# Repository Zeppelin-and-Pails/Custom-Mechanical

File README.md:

# Custom-Mechanical
Resources and tutorials for creating a custom mechanical keyboard

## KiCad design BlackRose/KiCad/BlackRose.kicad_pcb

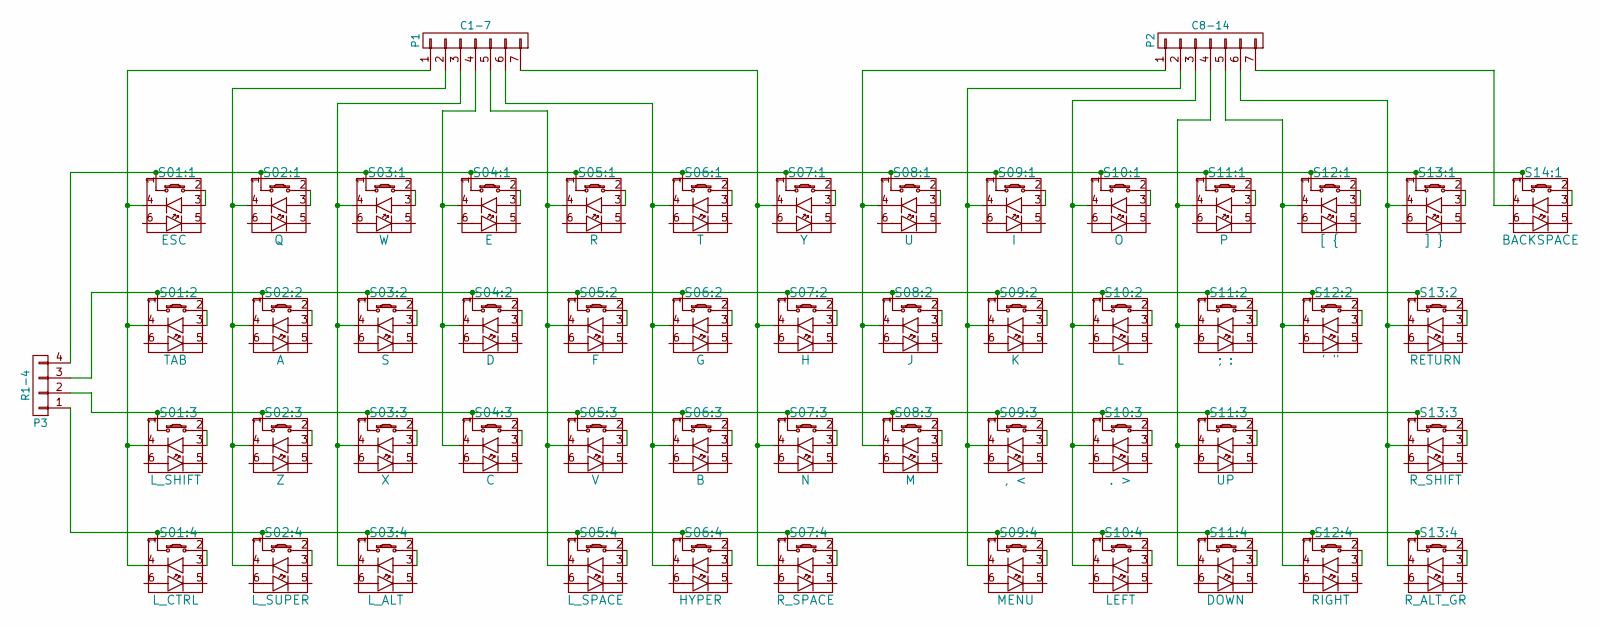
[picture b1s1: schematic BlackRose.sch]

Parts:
P1: C1-7; Pin_Header_Straight_1x07
P2: C8-14; Pin_Header_Straight_1x07
P3: R1-4; Pin_Header_Straight_1x04
S01:1: ESC; CHERRY_PCB_100H
S01:2: TAB; CHERRY_PCB_125H
S01:3: L_SHIFT; CHERRY_PCB_175H
S01:4: L_CTRL; CHERRY_PCB_125H
S02:1: Q; CHERRY_PCB_100H
S02:2: A; CHERRY_PCB_100H
S02:3: Z; CHERRY_PCB_100H
S02:4: L_SUPER; CHERRY_PCB_125H
S03:1: W; CHERRY_PCB_100H
S03:2: S; CHERRY_PCB_100H
S03:3: X; CHERRY_PCB_100H
S03:4: L_ALT; CHERRY_PCB_125H
S04:1: E; CHERRY_PCB_100H
S04:2: D; CHERRY_PCB_100H
S04:3: C; CHERRY_PCB_100H
S05:1: R; CHERRY_PCB_100H
S05:2: F; CHERRY_PCB_100H
S05:3: V; CHERRY_PCB_100H
S05:4: L_SPACE; CHERRY_PCB_200H
S06:1: T; CHERRY_PCB_100H
S06:2: G; CHERRY_PCB_100H
S06:3: B; CHERRY_PCB_100H
S06:4: HYPER; CHERRY_PCB_100H
S07:1: Y; CHERRY_PCB_100H
S07:2: H; CHERRY_PCB_100H
S07:3: N; CHERRY_PCB_100H
S07:4: R_SPACE; CHERRY_PCB_200H
S08:1: U; CHERRY_PCB_100H
S08:2: J; CHERRY_PCB_100H
S08:3: M; CHERRY_PCB_100H
S09:1: I; CHERRY_PCB_100H
S09:2: K; CHERRY_PCB_100H
S09:3: , <; CHERRY_PCB_100H
S09:4: MENU; CHERRY_PCB_100H
S10:1: O; CHERRY_PCB_100H
S10:2: L; CHERRY_PCB_100H
S10:3: . >; CHERRY_PCB_100H
S10:4: LEFT; CHERRY_PCB_100H
S11:1: P; CHERRY_PCB_100H
S11:2: ; :; CHERRY_PCB_100H
S11:3: UP; CHERRY_PCB_100H
S11:4: DOWN; CHERRY_PCB_100H
S12:1: [ {; CHERRY_PCB_100H
S12:2: ' \"; CHERRY_PCB_100H
S12:4: RIGHT; CHERRY_PCB_100H
S13:1: ] }; CHERRY_PCB_100H
S13:2: RETURN; CHERRY_PCB_175H
S13:3: R_SHIFT; CHERRY_PCB_225H
S13:4: R_ALT_GR; CHERRY_PCB_125H
S14:1: BACKSPACE; CHERRY_PCB_100H

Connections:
unnamed 0: P1.1, S01:1.4, S01:2.4, S01:3.4, S01:4.4; also elsewhere on the board
unnamed 1: P1.2, S02:1.4, S02:2.4, S02:3.4, S02:4.4; also elsewhere on the board
unnamed 2: P1.3, S03:1.4, S03:2.4, S03:3.4, S03:4.4; also elsewhere on the board
unnamed 3: P1.4, S04:1.4, S04:2.4, S04:3.4; also elsewhere on the board
unnamed 4: P1.5, S05:1.4, S05:2.4, S05:3.4, S05:4.4; also elsewhere on the board
unnamed 5: P1.6, S06:1.4, S06:2.4, S06:3.4, S06:4.4; also elsewhere on the board
unnamed 6: P1.7, S07:1.4, S07:2.4, S07:3.4, S07:4.4; also elsewhere on the board
unnamed 7: P2.1, S08:1.4, S08:2.4, S08:3.4; also elsewhere on the board
unnamed 8: P2.2, S09:1.4, S09:2.4, S09:3.4, S09:4.4; also elsewhere on the board
unnamed 9: P2.3, S10:1.4, S10:2.4, S10:3.4, S10:4.4; also elsewhere on the board
unnamed 10: P2.4, S11:1.4, S11:2.4, S11:3.4, S11:4.4; also elsewhere on the board
unnamed 11: P2.5, S12:1.4, S12:2.4, S12:4.4; also elsewhere on the board
unnamed 12: P2.6, S13:1.4, S13:2.4, S13:3.4, S13:4.4; also elsewhere on the board
unnamed 13: P2.7, S14:1.4; also elsewhere on the board
unnamed 14: P3.1, S01:4.1, S02:4.1, S03:4.1, S05:4.1, S06:4.1, S07:4.1, S09:4.1, S10:4.1, S11:4.1, S12:4.1, S13:4.1; also elsewhere on the board
unnamed 15: P3.2, S01:3.1, S02:3.1, S03:3.1, S04:3.1, S05:3.1, S06:3.1, S07:3.1, S08:3.1, S09:3.1, S10:3.1, S11:3.1, S13:3.1; also elsewhere on the board
unnamed 16: P3.3, S01:2.1, S02:2.1, S03:2.1, S04:2.1, S05:2.1, S06:2.1, S07:2.1, S08:2.1, S09:2.1, S10:2.1, S11:2.1, S12:2.1, S13:2.1; also elsewhere on the board
unnamed 17: P3.4, S01:1.1, S02:1.1, S03:1.1, S04:1.1, S05:1.1, S06:1.1, S07:1.1, S08:1.1, S09:1.1, S10:1.1, S11:1.1, S12:1.1, S13:1.1, S14:1.1; also elsewhere on the board
unnamed: S01:1.2, S01:1.3
unnamed: S01:2.2, S01:2.3
unnamed: S01:3.2, S01:3.3
unnamed: S01:4.2, S01:4.3
unnamed: S02:1.2, S02:1.3
unnamed: S02:2.2, S02:2.3
unnamed: S02:3.2, S02:3.3
unnamed: S02:4.2, S02:4.3
unnamed: S03:1.2, S03:1.3
unnamed: S03:2.2, S03:2.3
unnamed: S03:3.2, S03:3.3
unnamed: S03:4.2, S03:4.3
unnamed: S04:1.2, S04:1.3
unnamed: S04:2.2, S04:2.3
unnamed: S04:3.2, S04:3.3
unnamed: S05:1.2, S05:1.3
unnamed: S05:2.2, S05:2.3
unnamed: S05:3.2, S05:3.3
unnamed: S05:4.2, S05:4.3
unnamed: S06:1.2, S06:1.3
unnamed: S06:2.2, S06:2.3
unnamed: S06:3.2, S06:3.3
unnamed: S06:4.2, S06:4.3
unnamed: S07:1.2, S07:1.3
unnamed: S07:2.2, S07:2.3
unnamed: S07:3.2, S07:3.3
unnamed: S07:4.2, S07:4.3
unnamed: S08:1.2, S08:1.3
unnamed: S08:2.2, S08:2.3
unnamed: S08:3.2, S08:3.3
unnamed: S09:1.2, S09:1.3
unnamed: S09:2.2, S09:2.3
unnamed: S09:3.2, S09:3.3
unnamed: S09:4.2, S09:4.3
unnamed: S10:1.2, S10:1.3
unnamed: S10:2.2, S10:2.3
unnamed: S10:3.2, S10:3.3
unnamed: S10:4.2, S10:4.3
unnamed: S11:1.2, S11:1.3
unnamed: S11:2.2, S11:2.3
unnamed: S11:3.2, S11:3.3
unnamed: S11:4.2, S11:4.3
unnamed: S12:1.2, S12:1.3
unnamed: S12:2.2, S12:2.3
unnamed: S12:4.2, S12:4.3
unnamed: S13:1.2, S13:1.3
unnamed: S13:2.2, S13:2.3
unnamed: S13:3.2, S13:3.3
unnamed: S13:4.2, S13:4.3
unnamed: S14:1.2, S14:1.3

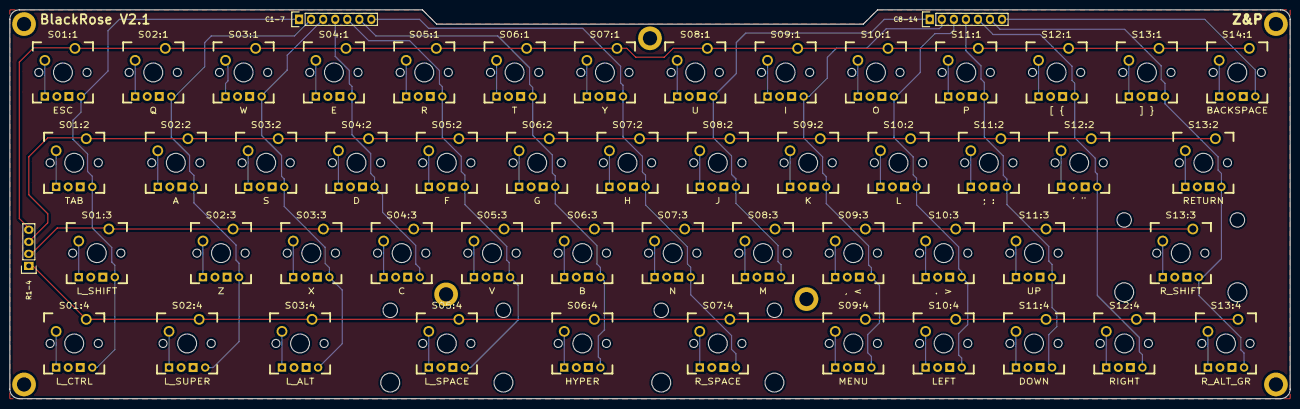
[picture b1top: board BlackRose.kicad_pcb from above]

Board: 2 copper layers, 270.0 x 82.0 mm, 53 parts (0 on the bottom side), 68 nets.

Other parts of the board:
C1-7: C1-7; Pin_Header_Straight_1x07
C8-14: C8-14; Pin_Header_Straight_1x07
R1-4: R1-4; Pin_Header_Straight_1x04

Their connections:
unnamed 0: C1-7.1; also elsewhere on the board
unnamed 1: C1-7.2; also elsewhere on the board
unnamed 2: C1-7.3; also elsewhere on the board
unnamed 3: C1-7.4; also elsewhere on the board
unnamed 4: C1-7.5; also elsewhere on the board
unnamed 5: C1-7.6; also elsewhere on the board
unnamed 6: C1-7.7; also elsewhere on the board
unnamed 7: C8-14.1; also elsewhere on the board
unnamed 8: C8-14.2; also elsewhere on the board
unnamed 9: C8-14.3; also elsewhere on the board
unnamed 10: C8-14.4; also elsewhere on the board
unnamed 11: C8-14.5; also elsewhere on the board
unnamed 12: C8-14.6; also elsewhere on the board
unnamed 13: C8-14.7; also elsewhere on the board
unnamed 14: R1-4.1; also elsewhere on the board
unnamed 15: R1-4.2; also elsewhere on the board
unnamed 16: R1-4.3; also elsewhere on the board
unnamed 17: R1-4.4; also elsewhere on the board

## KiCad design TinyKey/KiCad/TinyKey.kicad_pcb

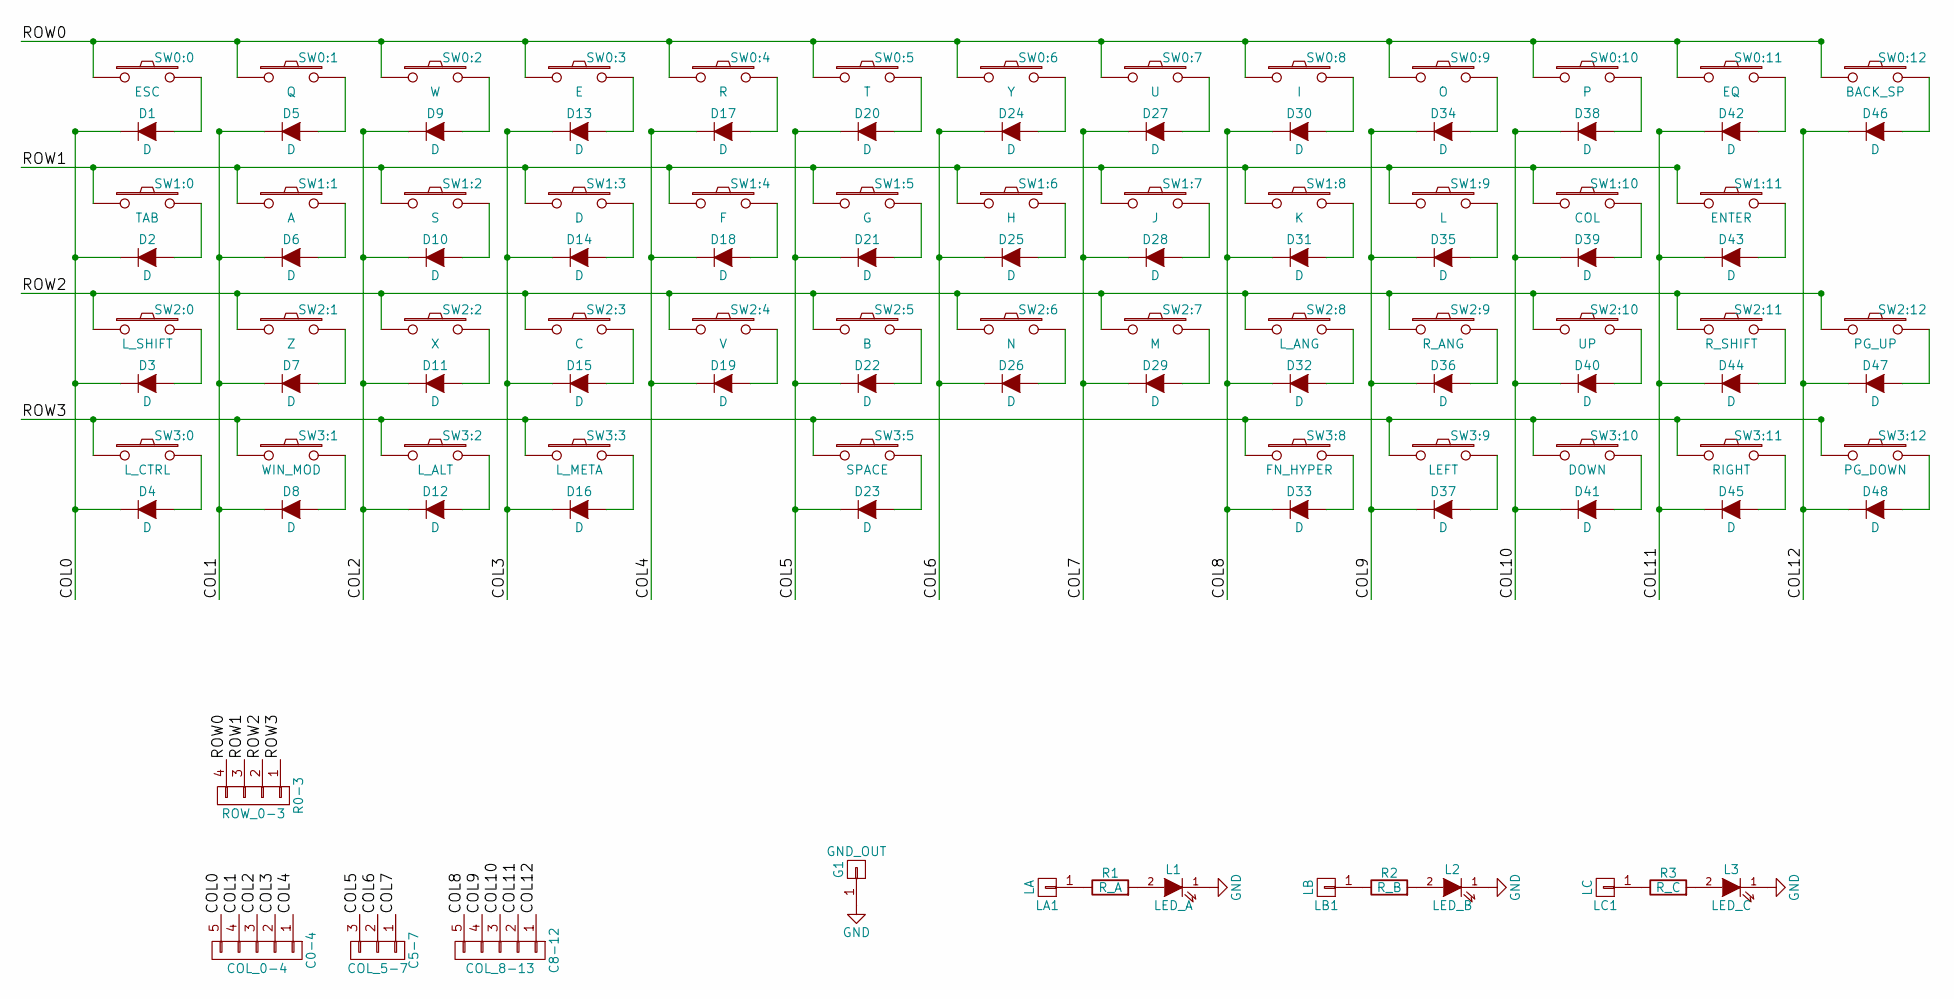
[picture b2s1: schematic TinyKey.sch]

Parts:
C0-4: COL_0-4; Pin_Header_Straight_1x05
C5-7: COL_5-7; Pin_Header_Straight_1x03
C8-12: COL_8-13; Pin_Header_Straight_1x05
D1, D2, D3, D4, D5, D6, D7, D8, D9, D10, D11, D12, D13, D14, D15, D16, D17, D18, D19, D20, D21, D22, D23, D24, D25, D26, D27, D28, D29, D30, D31, D32, D33, D34, D35, D36, D37, D38, D39, D40, D41, D42, D43, D44, D45, D46, D47, D48: D; DIODE
G1: GND_OUT; Pin_Header_Straight_1x01
L1: LED_A; LED_3MM
L2: LED_B; LED_3MM
L3: LED_C; LED_3MM
LA1: LA; Pin_Header_Straight_1x01
LB1: LB; Pin_Header_Straight_1x01
LC1: LC; Pin_Header_Straight_1x01
R0-3: ROW_0-3; Pin_Header_Straight_1x04
R1: R_A; RESISTOR
R2: R_B; RESISTOR
R3: R_C; RESISTOR
SW0:0: ESC; CHERRY_PCB_100H
SW0:1: Q; CHERRY_PCB_100H
SW0:2: W; CHERRY_PCB_100H
SW0:3: E; CHERRY_PCB_100H
SW0:4: R; CHERRY_PCB_100H
SW0:5: T; CHERRY_PCB_100H
SW0:6: Y; CHERRY_PCB_100H
SW0:7: U; CHERRY_PCB_100H
SW0:8: I; CHERRY_PCB_100H
SW0:9: O; CHERRY_PCB_100H
SW0:10: P; CHERRY_PCB_100H
SW0:11: EQ; CHERRY_PCB_100H
SW0:12: BACK_SP; CHERRY_PCB_150H
SW1:0: TAB; CHERRY_PCB_125H
SW1:1: A; CHERRY_PCB_100H
SW1:2: S; CHERRY_PCB_100H
SW1:3: D; CHERRY_PCB_100H
SW1:4: F; CHERRY_PCB_100H
SW1:5: G; CHERRY_PCB_100H
SW1:6: H; CHERRY_PCB_100H
SW1:7: J; CHERRY_PCB_100H
SW1:8: K; CHERRY_PCB_100H
SW1:9: L; CHERRY_PCB_100H
SW1:10: COL; CHERRY_PCB_100H
SW1:11: ENTER; CHERRY_PCB_225H
SW2:0: L_SHIFT; CHERRY_PCB_175H
SW2:1: Z; CHERRY_PCB_100H
SW2:2: X; CHERRY_PCB_100H
SW2:3: C; CHERRY_PCB_100H
SW2:4: V; CHERRY_PCB_100H
SW2:5: B; CHERRY_PCB_100H
SW2:6: N; CHERRY_PCB_100H
SW2:7: M; CHERRY_PCB_100H
SW2:8: L_ANG; CHERRY_PCB_100H
SW2:9: R_ANG; CHERRY_PCB_100H
SW2:10: UP; CHERRY_PCB_100H
SW2:11: R_SHIFT; CHERRY_PCB_175H
SW2:12: PG_UP; KSA_Tactile_SPST
SW3:0: L_CTRL; CHERRY_PCB_100H
SW3:1: WIN_MOD; CHERRY_PCB_100H
SW3:2: L_ALT; CHERRY_PCB_100H
SW3:3: L_META; CHERRY_PCB_125H
SW3:5: SPACE; CHERRY_PCB_425H
SW3:8: FN_HYPER; CHERRY_PCB_125H
SW3:9: LEFT; CHERRY_PCB_100H
SW3:10: DOWN; CHERRY_PCB_100H
SW3:11: RIGHT; CHERRY_PCB_100H
SW3:12: PG_DOWN; KSA_Tactile_SPST

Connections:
/COL0: C0-4.5, D1.1 (K), D2.1 (K), D3.1 (K), D4.1 (K)
/COL1: C0-4.4, D5.1 (K), D6.1 (K), D7.1 (K), D8.1 (K)
/COL2: C0-4.3, D9.1 (K), D10.1 (K), D11.1 (K), D12.1 (K)
/COL3: C0-4.2, D13.1 (K), D14.1 (K), D15.1 (K), D16.1 (K)
/COL4: C0-4.1, D17.1 (K), D18.1 (K), D19.1 (K)
/COL5: C5-7.3, D20.1 (K), D21.1 (K), D22.1 (K), D23.1 (K)
/COL6: C5-7.2, D24.1 (K), D25.1 (K), D26.1 (K)
/COL7: C5-7.1, D27.1 (K), D28.1 (K), D29.1 (K)
/COL8: C8-12.5, D30.1 (K), D31.1 (K), D32.1 (K), D33.1 (K)
/COL9: C8-12.4, D34.1 (K), D35.1 (K), D36.1 (K), D37.1 (K)
/COL10: C8-12.3, D38.1 (K), D39.1 (K), D40.1 (K), D41.1 (K)
/COL11: C8-12.2, D42.1 (K), D43.1 (K), D44.1 (K), D45.1 (K)
/COL12: C8-12.1, D46.1 (K), D47.1 (K), D48.1 (K)
/ROW0: R0-3.4, SW0:0.1, SW0:1.1, SW0:2.1, SW0:3.1, SW0:4.1, SW0:5.1, SW0:6.1, SW0:7.1, SW0:8.1, SW0:9.1, SW0:10.1, SW0:11.1, SW0:12.1
/ROW1: R0-3.3, SW1:0.1, SW1:1.1, SW1:2.1, SW1:3.1, SW1:4.1, SW1:5.1, SW1:6.1, SW1:7.1, SW1:8.1, SW1:9.1, SW1:10.1, SW1:11.1
/ROW2: R0-3.2, SW2:0.1, SW2:1.1, SW2:2.1, SW2:3.1, SW2:4.1, SW2:5.1, SW2:6.1, SW2:7.1, SW2:8.1, SW2:9.1, SW2:10.1, SW2:11.1, SW2:12.1
/ROW3: R0-3.1, SW3:0.1, SW3:1.1, SW3:2.1, SW3:3.1, SW3:5.1, SW3:8.1, SW3:9.1, SW3:10.1, SW3:11.1, SW3:12.1
GND: G1.1, L1.1 (K), L2.1 (K), L3.1 (K)
unnamed: D1.2 (A), SW0:0.2
unnamed: D2.2 (A), SW1:0.2
unnamed: D3.2 (A), SW2:0.2
unnamed: D4.2 (A), SW3:0.2
unnamed: D5.2 (A), SW0:1.2
unnamed: D6.2 (A), SW1:1.2
unnamed: D7.2 (A), SW2:1.2
unnamed: D8.2 (A), SW3:1.2
unnamed: D9.2 (A), SW0:2.2
unnamed: D10.2 (A), SW1:2.2
unnamed: D11.2 (A), SW2:2.2
unnamed: D12.2 (A), SW3:2.2
unnamed: D13.2 (A), SW0:3.2
unnamed: D14.2 (A), SW1:3.2
unnamed: D15.2 (A), SW2:3.2
unnamed: D16.2 (A), SW3:3.2
unnamed: D17.2 (A), SW0:4.2
unnamed: D18.2 (A), SW1:4.2
unnamed: D19.2 (A), SW2:4.2
unnamed: D20.2 (A), SW0:5.2
unnamed: D21.2 (A), SW1:5.2
unnamed: D22.2 (A), SW2:5.2
unnamed: D23.2 (A), SW3:5.2
unnamed: D24.2 (A), SW0:6.2
unnamed: D25.2 (A), SW1:6.2
unnamed: D26.2 (A), SW2:6.2
unnamed: D27.2 (A), SW0:7.2
unnamed: D28.2 (A), SW1:7.2
unnamed: D29.2 (A), SW2:7.2
unnamed: D30.2 (A), SW0:8.2
unnamed: D31.2 (A), SW1:8.2
unnamed: D32.2 (A), SW2:8.2
unnamed: D33.2 (A), SW3:8.2
unnamed: D34.2 (A), SW0:9.2
unnamed: D35.2 (A), SW1:9.2
unnamed: D36.2 (A), SW2:9.2
unnamed: D37.2 (A), SW3:9.2
unnamed: D38.2 (A), SW0:10.2
unnamed: D39.2 (A), SW1:10.2
unnamed: D40.2 (A), SW2:10.2
unnamed: D41.2 (A), SW3:10.2
unnamed: D42.2 (A), SW0:11.2
unnamed: D43.2 (A), SW1:11.2
unnamed: D44.2 (A), SW2:11.2
unnamed: D45.2 (A), SW3:11.2
unnamed: D46.2 (A), SW0:12.2
unnamed: D47.2 (A), SW2:12.2
unnamed: D48.2 (A), SW3:12.2
unnamed: L1.2 (A), R1.2
unnamed: L2.2 (A), R2.2
unnamed: L3.2 (A), R3.2
unnamed: LA1.1, R1.1
unnamed: LB1.1, R2.1
unnamed: LC1.1, R3.1

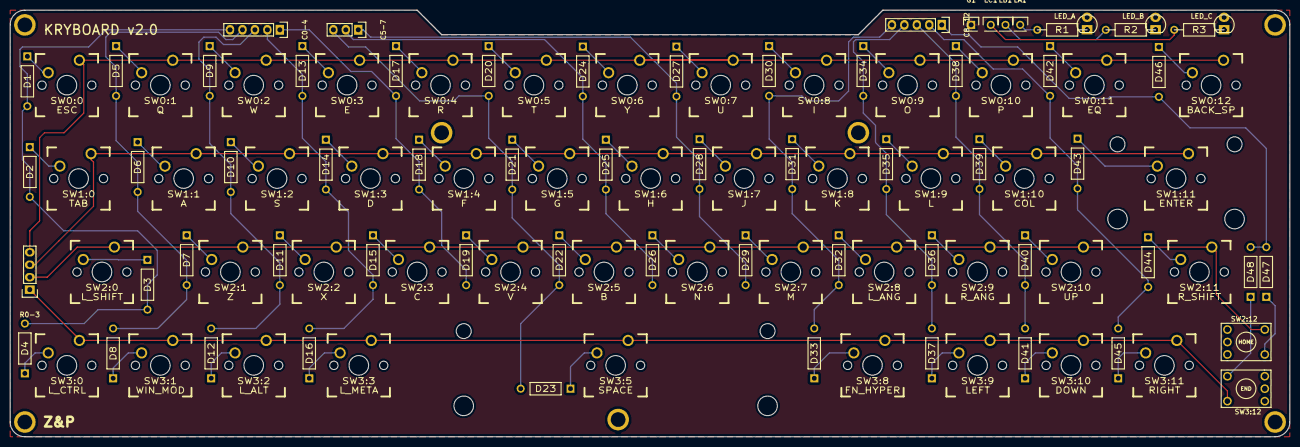
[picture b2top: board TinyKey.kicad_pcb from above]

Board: 2 copper layers, 261.0 x 87.0 mm, 110 parts (0 on the bottom side), 72 nets.

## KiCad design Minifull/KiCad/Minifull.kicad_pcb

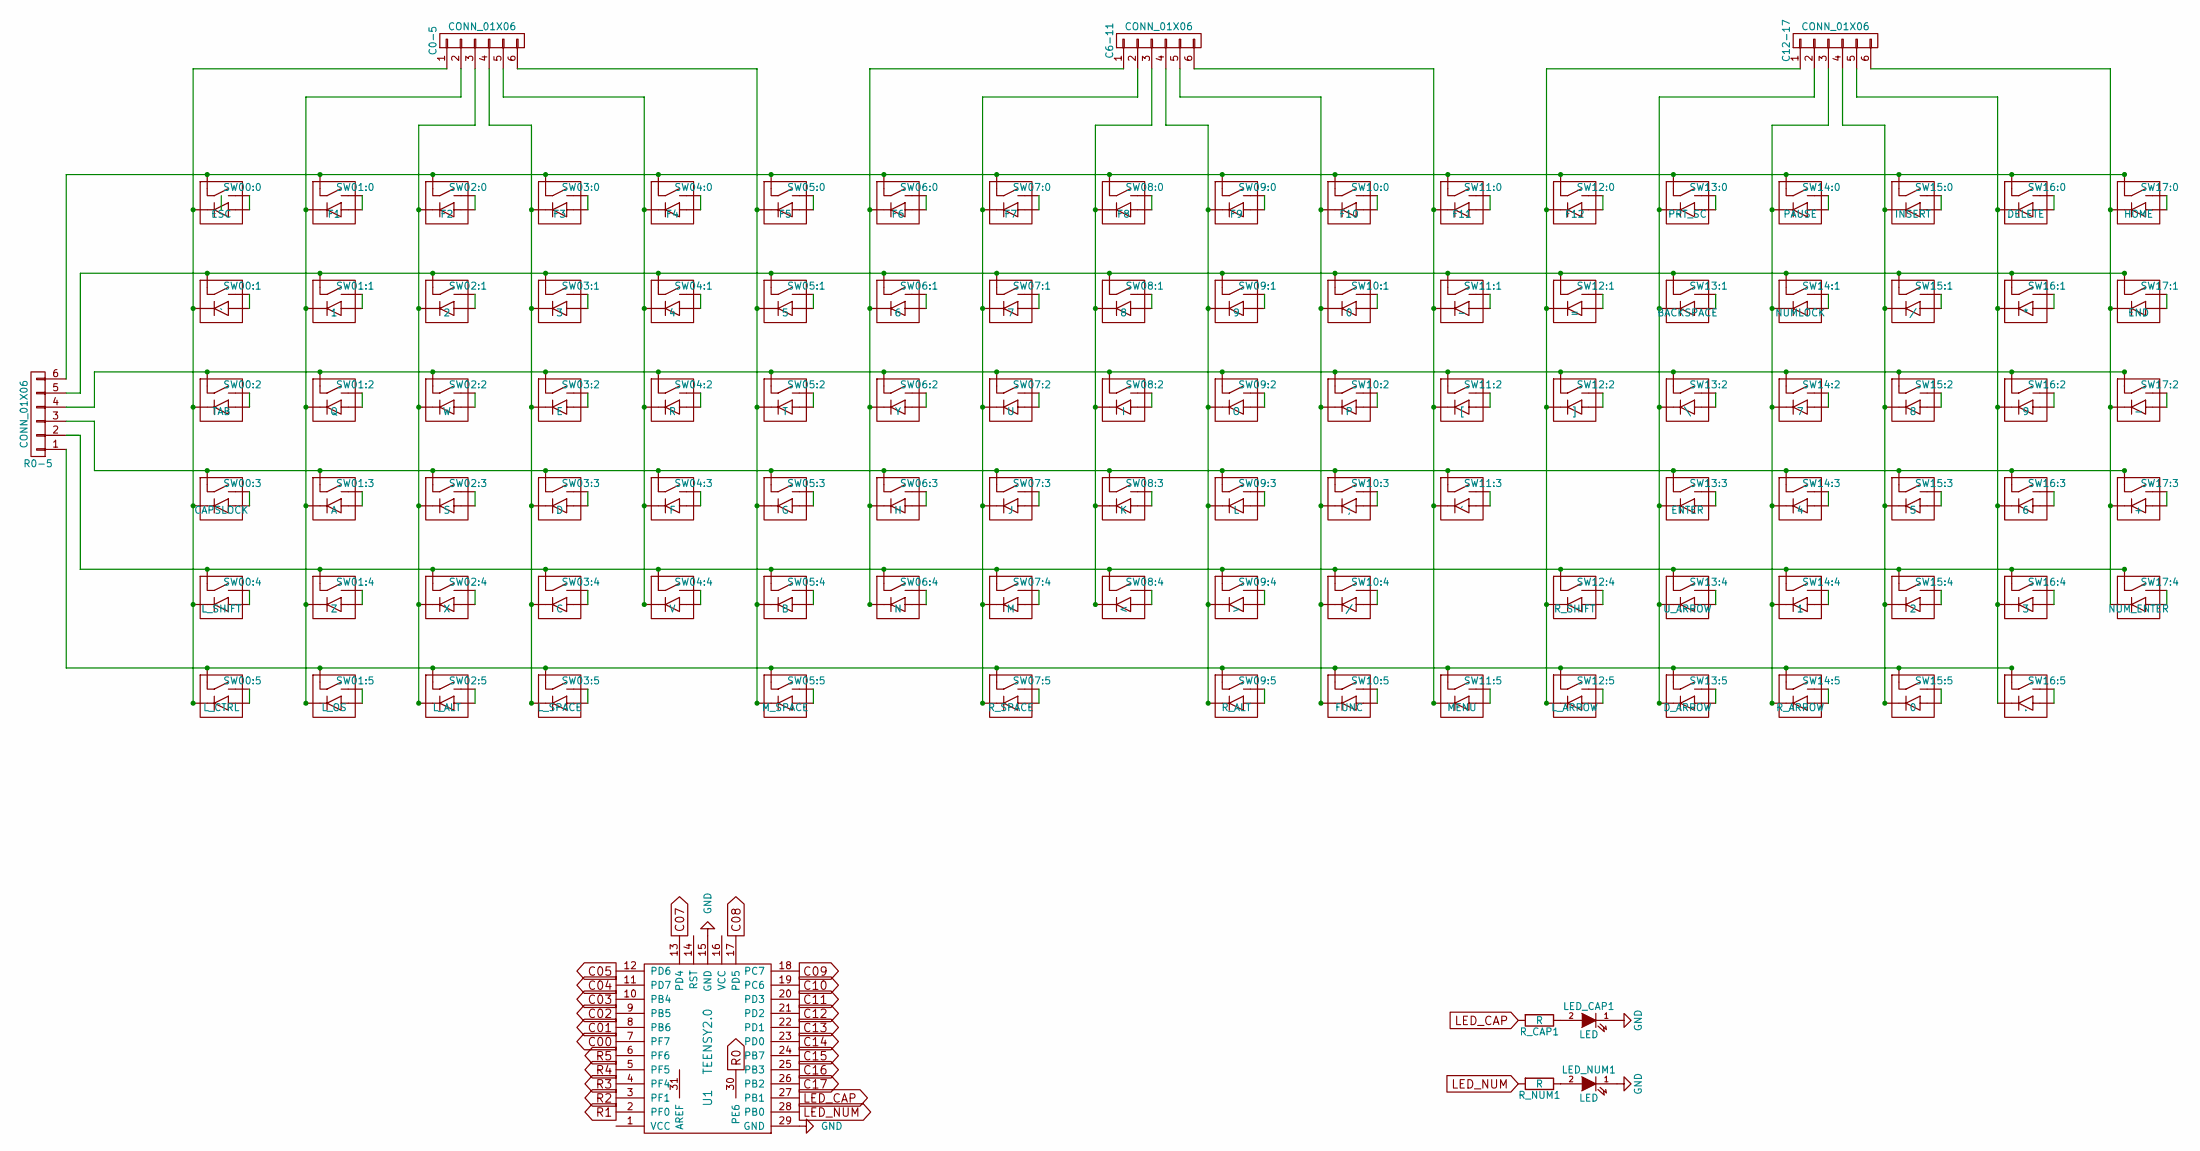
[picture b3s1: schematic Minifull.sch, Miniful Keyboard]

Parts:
C0-5, C6-11, C12-17: CONN_01X06; Pin_Header_Angled_1x06
LED_CAP1: LED; LED_3MM
LED_NUM1: LED; LED_3MM
R0-5: CONN_01X06; Pin_Header_Angled_1x06
R_CAP1: R; RESISTOR
R_NUM1: R; RESISTOR
SW00:0: ESC; CHERRY_PCB_100H
SW00:1: `; CHERRY_PCB_100H
SW00:2: TAB; CHERRY_PCB_150H
SW00:3: CAPSLOCK; CHERRY_PCB_175H
SW00:4: L_SHIFT; CHERRY_PCB_225H
SW00:5: L_CTRL; CHERRY_PCB_125H
SW01:0: F1; CHERRY_PCB_100H
SW01:1, SW14:4: 1; CHERRY_PCB_100H
SW01:2: Q; CHERRY_PCB_100H
SW01:3: A; CHERRY_PCB_100H
SW01:4: Z; CHERRY_PCB_100H
SW01:5: L_OS; CHERRY_PCB_125H
SW02:0: F2; CHERRY_PCB_100H
SW02:1, SW15:4: 2; CHERRY_PCB_100H
SW02:2: W; CHERRY_PCB_100H
SW02:3: S; CHERRY_PCB_100H
SW02:4: X; CHERRY_PCB_100H
SW02:5: L_ALT; CHERRY_PCB_125H
SW03:0: F3; CHERRY_PCB_100H
SW03:1, SW16:4: 3; CHERRY_PCB_100H
SW03:2: E; CHERRY_PCB_100H
SW03:3: D; CHERRY_PCB_100H
SW03:4: C; CHERRY_PCB_100H
SW03:5: L_SPACE; CHERRY_PCB_200H
SW04:0: F4; CHERRY_PCB_100H
SW04:1, SW14:3: 4; CHERRY_PCB_100H
SW04:2: R; CHERRY_PCB_100H
SW04:3: F; CHERRY_PCB_100H
SW04:4: V; CHERRY_PCB_100H
SW05:0: F5; CHERRY_PCB_100H
SW05:1, SW15:3: 5; CHERRY_PCB_100H
SW05:2: T; CHERRY_PCB_100H
SW05:3: G; CHERRY_PCB_100H
SW05:4: B; CHERRY_PCB_100H
SW05:5: M_SPACE; CHERRY_PCB_200H
SW06:0: F6; CHERRY_PCB_100H
SW06:1, SW16:3: 6; CHERRY_PCB_100H
SW06:2: Y; CHERRY_PCB_100H
SW06:3: H; CHERRY_PCB_100H
SW06:4: N; CHERRY_PCB_100H
SW07:0: F7; CHERRY_PCB_100H
SW07:1, SW14:2: 7; CHERRY_PCB_100H
SW07:2: U; CHERRY_PCB_100H
SW07:3: J; CHERRY_PCB_100H
SW07:4: M; CHERRY_PCB_100H
SW07:5: R_SPACE; CHERRY_PCB_200H
SW08:0: F8; CHERRY_PCB_100H
SW08:1, SW15:2: 8; CHERRY_PCB_100H
SW08:2: I; CHERRY_PCB_100H
SW08:3: K; CHERRY_PCB_100H
SW08:4: <; CHERRY_PCB_100H
SW09:0: F9; CHERRY_PCB_100H
SW09:1, SW16:2: 9; CHERRY_PCB_100H
SW09:2: O; CHERRY_PCB_100H
SW09:3: L; CHERRY_PCB_100H
SW09:4: >; CHERRY_PCB_100H
SW09:5: R_ALT; CHERRY_PCB_100H
SW10:0: F10; CHERRY_PCB_100H
SW10:1, SW15:5: 0; CHERRY_PCB_100H
SW10:2: P; CHERRY_PCB_100H
SW10:3: ;; CHERRY_PCB_100H
SW10:4, SW15:1: /; CHERRY_PCB_100H
SW10:5: FUNC; CHERRY_PCB_100H
SW11:0: F11; CHERRY_PCB_100H
SW11:1, SW17:2: -; CHERRY_PCB_100H
SW11:2: [; CHERRY_PCB_100H
SW11:3: '; CHERRY_PCB_100H
SW11:5: MENU; CHERRY_PCB_125H
SW12:0: F12; CHERRY_PCB_100H
SW12:1: =; CHERRY_PCB_100H
SW12:2: ]; CHERRY_PCB_100H
SW12:4: R_SHIFT; CHERRY_PCB_175H
SW12:5: L_ARROW; CHERRY_PCB_100H
SW13:0: PRT_SC; CHERRY_PCB_100H
SW13:1: BACKSPACE; CHERRY_PCB_200H
SW13:2: \\; CHERRY_PCB_100H
SW13:3: ENTER; CHERRY_PCB_225H
SW13:4: U_ARROW; CHERRY_PCB_100H
SW13:5: D_ARROW; CHERRY_PCB_100H
SW14:0: PAUSE; CHERRY_PCB_100H
SW14:1: NUMLOCK; CHERRY_PCB_100H
SW14:5: R_ARROW; CHERRY_PCB_100H
SW15:0: INSERT; CHERRY_PCB_100H
SW16:0: DELETE; CHERRY_PCB_100H
SW16:1: *; CHERRY_PCB_100H
SW16:5: .; CHERRY_PCB_100H
SW17:0: HOME; CHERRY_PCB_100H
SW17:1: END; CHERRY_PCB_100H
SW17:3: +; CHERRY_PCB_200V
SW17:4: NUM_ENTER; CHERRY_PCB_200V
U1: TEENSY2.0; TEENSY_2.0

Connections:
GND: LED_CAP1.1 (K), LED_NUM1.1 (K), U1.15 (GND), U1.29 (GND)
LED_CAP: R_CAP1.2, U1.27 (PB1)
LED_NUM: R_NUM1.2, U1.28 (PB0)
unnamed: C0-5.1, SW00:0.4 (D), SW00:1.4 (D), SW00:2.4 (D), SW00:3.4 (D), SW00:4.4 (D), SW00:5.4 (D)
unnamed: C0-5.2, SW01:0.4 (D), SW01:1.4 (D), SW01:2.4 (D), SW01:3.4 (D), SW01:4.4 (D), SW01:5.4 (D)
unnamed: C0-5.3, SW02:0.4 (D), SW02:1.4 (D), SW02:2.4 (D), SW02:3.4 (D), SW02:4.4 (D), SW02:5.4 (D)
unnamed: C0-5.4, SW03:0.4 (D), SW03:1.4 (D), SW03:2.4 (D), SW03:3.4 (D), SW03:4.4 (D), SW03:5.4 (D)
unnamed: C0-5.5, SW04:0.4 (D), SW04:1.4 (D), SW04:2.4 (D), SW04:3.4 (D), SW04:4.4 (D)
unnamed: C0-5.6, SW05:0.4 (D), SW05:1.4 (D), SW05:2.4 (D), SW05:3.4 (D), SW05:4.4 (D), SW05:5.4 (D)
unnamed: C6-11.1, SW06:0.4 (D), SW06:1.4 (D), SW06:2.4 (D), SW06:3.4 (D), SW06:4.4 (D)
unnamed: C6-11.2, SW07:0.4 (D), SW07:1.4 (D), SW07:2.4 (D), SW07:3.4 (D), SW07:4.4 (D), SW07:5.4 (D)
unnamed: C6-11.3, SW08:0.4 (D), SW08:1.4 (D), SW08:2.4 (D), SW08:3.4 (D), SW08:4.4 (D)
unnamed: C6-11.4, SW09:0.4 (D), SW09:1.4 (D), SW09:2.4 (D), SW09:3.4 (D), SW09:4.4 (D), SW09:5.4 (D)
unnamed: C6-11.5, SW10:0.4 (D), SW10:1.4 (D), SW10:2.4 (D), SW10:3.4 (D), SW10:4.4 (D), SW10:5.4 (D)
unnamed: C6-11.6, SW11:0.4 (D), SW11:1.4 (D), SW11:2.4 (D), SW11:3.4 (D), SW11:5.4 (D)
unnamed: C12-17.1, SW12:0.4 (D), SW12:1.4 (D), SW12:2.4 (D), SW12:4.4 (D), SW12:5.4 (D)
unnamed: C12-17.2, SW13:0.4 (D), SW13:1.4 (D), SW13:2.4 (D), SW13:3.4 (D), SW13:4.4 (D), SW13:5.4 (D)
unnamed: C12-17.3, SW14:0.4 (D), SW14:1.4 (D), SW14:2.4 (D), SW14:3.4 (D), SW14:4.4 (D), SW14:5.4 (D)
unnamed: C12-17.4, SW15:0.4 (D), SW15:1.4 (D), SW15:2.4 (D), SW15:3.4 (D), SW15:4.4 (D), SW15:5.4 (D)
unnamed: C12-17.5, SW16:0.4 (D), SW16:1.4 (D), SW16:2.4 (D), SW16:3.4 (D), SW16:4.4 (D), SW16:5.4 (D)
unnamed: C12-17.6, SW17:0.4 (D), SW17:1.4 (D), SW17:2.4 (D), SW17:3.4 (D), SW17:4.4 (D)
unnamed: LED_CAP1.2 (A), R_CAP1.1
unnamed: LED_NUM1.2 (A), R_NUM1.1
unnamed: R0-5.1, SW00:5.1 (A), SW01:5.1 (A), SW02:5.1 (A), SW03:5.1 (A), SW05:5.1 (A), SW07:5.1 (A), SW09:5.1 (A), SW10:5.1 (A), SW11:5.1 (A), SW12:5.1 (A), SW13:5.1 (A), SW14:5.1 (A), SW15:5.1 (A), SW16:5.1 (A)
unnamed: R0-5.2, SW00:4.1 (A), SW01:4.1 (A), SW02:4.1 (A), SW03:4.1 (A), SW04:4.1 (A), SW05:4.1 (A), SW06:4.1 (A), SW07:4.1 (A), SW08:4.1 (A), SW09:4.1 (A), SW10:4.1 (A), SW12:4.1 (A), SW13:4.1 (A), SW14:4.1 (A), SW15:4.1 (A), SW16:4.1 (A), SW17:4.1 (A)
unnamed: R0-5.3, SW00:3.1 (A), SW01:3.1 (A), SW02:3.1 (A), SW03:3.1 (A), SW04:3.1 (A), SW05:3.1 (A), SW06:3.1 (A), SW07:3.1 (A), SW08:3.1 (A), SW09:3.1 (A), SW10:3.1 (A), SW11:3.1 (A), SW13:3.1 (A), SW14:3.1 (A), SW15:3.1 (A), SW16:3.1 (A), SW17:3.1 (A)
unnamed: R0-5.4, SW00:2.1 (A), SW01:2.1 (A), SW02:2.1 (A), SW03:2.1 (A), SW04:2.1 (A), SW05:2.1 (A), SW06:2.1 (A), SW07:2.1 (A), SW08:2.1 (A), SW09:2.1 (A), SW10:2.1 (A), SW11:2.1 (A), SW12:2.1 (A), SW13:2.1 (A), SW14:2.1 (A), SW15:2.1 (A), SW16:2.1 (A), SW17:2.1 (A)
unnamed: R0-5.5, SW00:1.1 (A), SW01:1.1 (A), SW02:1.1 (A), SW03:1.1 (A), SW04:1.1 (A), SW05:1.1 (A), SW06:1.1 (A), SW07:1.1 (A), SW08:1.1 (A), SW09:1.1 (A), SW10:1.1 (A), SW11:1.1 (A), SW12:1.1 (A), SW13:1.1 (A), SW14:1.1 (A), SW15:1.1 (A), SW16:1.1 (A), SW17:1.1 (A)
unnamed: R0-5.6, SW00:0.1 (A), SW01:0.1 (A), SW02:0.1 (A), SW03:0.1 (A), SW04:0.1 (A), SW05:0.1 (A), SW06:0.1 (A), SW07:0.1 (A), SW08:0.1 (A), SW09:0.1 (A), SW10:0.1 (A), SW11:0.1 (A), SW12:0.1 (A), SW13:0.1 (A), SW14:0.1 (A), SW15:0.1 (A), SW16:0.1 (A), SW17:0.1 (A)
unnamed: SW00:0.2 (B), SW00:0.3 (B)
unnamed: SW00:1.2 (B), SW00:1.3 (B)
unnamed: SW00:2.2 (B), SW00:2.3 (B)
unnamed: SW00:3.2 (B), SW00:3.3 (B)
unnamed: SW00:4.2 (B), SW00:4.3 (B)
unnamed: SW00:5.2 (B), SW00:5.3 (B)
unnamed: SW01:0.2 (B), SW01:0.3 (B)
unnamed: SW01:1.2 (B), SW01:1.3 (B)
unnamed: SW01:2.2 (B), SW01:2.3 (B)
unnamed: SW01:3.2 (B), SW01:3.3 (B)
unnamed: SW01:4.2 (B), SW01:4.3 (B)
unnamed: SW01:5.2 (B), SW01:5.3 (B)
unnamed: SW02:0.2 (B), SW02:0.3 (B)
unnamed: SW02:1.2 (B), SW02:1.3 (B)
unnamed: SW02:2.2 (B), SW02:2.3 (B)
unnamed: SW02:3.2 (B), SW02:3.3 (B)
unnamed: SW02:4.2 (B), SW02:4.3 (B)
unnamed: SW02:5.2 (B), SW02:5.3 (B)
unnamed: SW03:0.2 (B), SW03:0.3 (B)
unnamed: SW03:1.2 (B), SW03:1.3 (B)
unnamed: SW03:2.2 (B), SW03:2.3 (B)
unnamed: SW03:3.2 (B), SW03:3.3 (B)
unnamed: SW03:4.2 (B), SW03:4.3 (B)
unnamed: SW03:5.2 (B), SW03:5.3 (B)
unnamed: SW04:0.2 (B), SW04:0.3 (B)
unnamed: SW04:1.2 (B), SW04:1.3 (B)
unnamed: SW04:2.2 (B), SW04:2.3 (B)
unnamed: SW04:3.2 (B), SW04:3.3 (B)
unnamed: SW04:4.2 (B), SW04:4.3 (B)
unnamed: SW05:0.2 (B), SW05:0.3 (B)
unnamed: SW05:1.2 (B), SW05:1.3 (B)
unnamed: SW05:2.2 (B), SW05:2.3 (B)
unnamed: SW05:3.2 (B), SW05:3.3 (B)
unnamed: SW05:4.2 (B), SW05:4.3 (B)
unnamed: SW05:5.2 (B), SW05:5.3 (B)
unnamed: SW06:0.2 (B), SW06:0.3 (B)
unnamed: SW06:1.2 (B), SW06:1.3 (B)
unnamed: SW06:2.2 (B), SW06:2.3 (B)
unnamed: SW06:3.2 (B), SW06:3.3 (B)
unnamed: SW06:4.2 (B), SW06:4.3 (B)
unnamed: SW07:0.2 (B), SW07:0.3 (B)
unnamed: SW07:1.2 (B), SW07:1.3 (B)
unnamed: SW07:2.2 (B), SW07:2.3 (B)
unnamed: SW07:3.2 (B), SW07:3.3 (B)
unnamed: SW07:4.2 (B), SW07:4.3 (B)
unnamed: SW07:5.2 (B), SW07:5.3 (B)
unnamed: SW08:0.2 (B), SW08:0.3 (B)
unnamed: SW08:1.2 (B), SW08:1.3 (B)
unnamed: SW08:2.2 (B), SW08:2.3 (B)
unnamed: SW08:3.2 (B), SW08:3.3 (B)
unnamed: SW08:4.2 (B), SW08:4.3 (B)
unnamed: SW09:0.2 (B), SW09:0.3 (B)
unnamed: SW09:1.2 (B), SW09:1.3 (B)
unnamed: SW09:2.2 (B), SW09:2.3 (B)
unnamed: SW09:3.2 (B), SW09:3.3 (B)
unnamed: SW09:4.2 (B), SW09:4.3 (B)
unnamed: SW09:5.2 (B), SW09:5.3 (B)
unnamed: SW10:0.2 (B), SW10:0.3 (B)
unnamed: SW10:1.2 (B), SW10:1.3 (B)
unnamed: SW10:2.2 (B), SW10:2.3 (B)
unnamed: SW10:3.2 (B), SW10:3.3 (B)
unnamed: SW10:4.2 (B), SW10:4.3 (B)
unnamed: SW10:5.2 (B), SW10:5.3 (B)
unnamed: SW11:0.2 (B), SW11:0.3 (B)
unnamed: SW11:1.2 (B), SW11:1.3 (B)
unnamed: SW11:2.2 (B), SW11:2.3 (B)
unnamed: SW11:3.2 (B), SW11:3.3 (B)
unnamed: SW11:5.2 (B), SW11:5.3 (B)
unnamed: SW12:0.2 (B), SW12:0.3 (B)
unnamed: SW12:1.2 (B), SW12:1.3 (B)
unnamed: SW12:2.2 (B), SW12:2.3 (B)
unnamed: SW12:4.2 (B), SW12:4.3 (B)
unnamed: SW12:5.2 (B), SW12:5.3 (B)
unnamed: SW13:0.2 (B), SW13:0.3 (B)
unnamed: SW13:1.2 (B), SW13:1.3 (B)
unnamed: SW13:2.2 (B), SW13:2.3 (B)
unnamed: SW13:3.2 (B), SW13:3.3 (B)
unnamed: SW13:4.2 (B), SW13:4.3 (B)
unnamed: SW13:5.2 (B), SW13:5.3 (B)
unnamed: SW14:0.2 (B), SW14:0.3 (B)
unnamed: SW14:1.2 (B), SW14:1.3 (B)
unnamed: SW14:2.2 (B), SW14:2.3 (B)
unnamed: SW14:3.2 (B), SW14:3.3 (B)
unnamed: SW14:4.2 (B), SW14:4.3 (B)
unnamed: SW14:5.2 (B), SW14:5.3 (B)
unnamed: SW15:0.2 (B), SW15:0.3 (B)
unnamed: SW15:1.2 (B), SW15:1.3 (B)
unnamed: SW15:2.2 (B), SW15:2.3 (B)
unnamed: SW15:3.2 (B), SW15:3.3 (B)
unnamed: SW15:4.2 (B), SW15:4.3 (B)
unnamed: SW15:5.2 (B), SW15:5.3 (B)
unnamed: SW16:0.2 (B), SW16:0.3 (B)
unnamed: SW16:1.2 (B), SW16:1.3 (B)
unnamed: SW16:2.2 (B), SW16:2.3 (B)
unnamed: SW16:3.2 (B), SW16:3.3 (B)
unnamed: SW16:4.2 (B), SW16:4.3 (B)
unnamed: SW16:5.2 (B), SW16:5.3 (B)
unnamed: SW17:0.2 (B), SW17:0.3 (B)
unnamed: SW17:1.2 (B), SW17:1.3 (B)
unnamed: SW17:2.2 (B), SW17:2.3 (B)
unnamed: SW17:3.2 (B), SW17:3.3 (B)
unnamed: SW17:4.2 (B), SW17:4.3 (B)

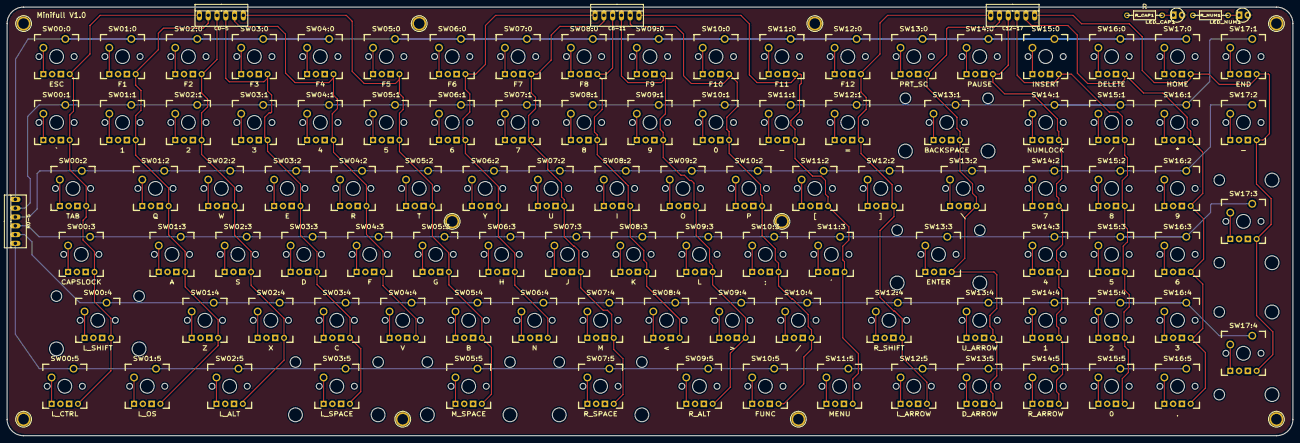
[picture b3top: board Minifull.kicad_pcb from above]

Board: 2 copper layers, 371.5 x 123.8 mm, 110 parts (0 on the bottom side), 129 nets.

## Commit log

2016-10-04 Adding gerber for KryBoard V1
2016-10-04 Adding key
2016-10-04 Adding row 1 keys
2016-10-04 Adding row 2 keys
2016-10-04 KMR: adding dxf and stl files
2016-10-04 Adding row 3 keys
2016-10-04 KMR: adding KiCad files
2016-10-04 Adding footprints for KiCad
2016-10-04 Tidy up
2016-10-04 Support board JIC
2016-10-05 KMR: cleaning up folders
2016-10-05 KMR: adding in extra spacebar footprints
2016-10-05 Correcting naming
2016-10-06 Making space for teensy
2016-10-27 Adding Minifull and reworking folder structure
2016-10-27 Adding layout images
2016-11-11 Adding BlackRose, updating switches comp lib
2016-11-16 Adding DXF and SVG for BlackRose
2016-11-23 BlackRose V1 complete, Updated TinyKey to V2
2018-10-17 Add outline model
2018-10-17 Add dogbone
2018-10-17 Add baseplate
2018-10-17 Add keybrace
2018-10-17 Add spacer
